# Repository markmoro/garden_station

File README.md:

Garden Station
==============

Single board garden watering controller based on Arduino.

This is a single board AT-MEGA controller.   This has an interface for a display, some LED indicators, inputs for moisture sensors and outputs for servo controller valves.   

Code is now added and the board has now been replaced with an SMD version.  The original prototype board is in the old folder, however there are some wiring issues with the shift registers which require some jumper wire.   This can be seen on the blog page photo.

More details are available on [http://makicity.com/](http://makicity.com/)

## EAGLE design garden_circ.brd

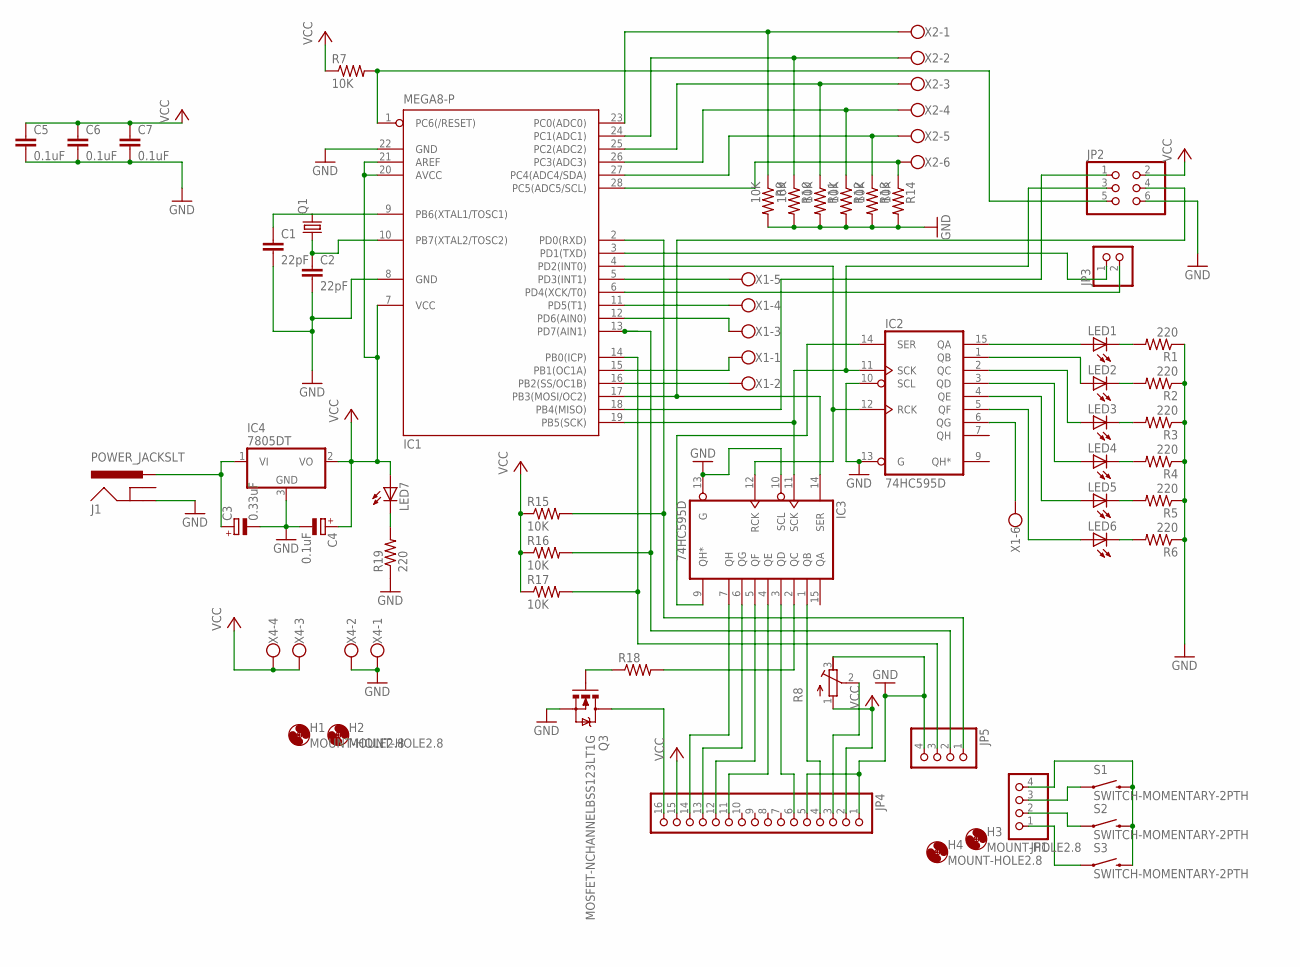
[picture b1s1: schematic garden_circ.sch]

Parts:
C1, C2: 22pF; 0805
C3: 0.33uF; SMC_C
C4: 0.1uF; SMC_C
C5, C6, C7: 0.1uF; 0805
H1, H2, H3, H4: MOUNT-HOLE2.8; 2,8
IC1: MEGA8-P; DIL28-3
IC2, IC3: 74HC595D; SO16
IC4: 7805DT; TO252
J1: POWER_JACKSLT; POWER_JACK_SLOT
JP1, JP5: PINHD-1X4; 1X04
JP2: PINHD-2X3; 2X03
JP3: PINHD-1X2; 1X02
JP4: PINHD-1X16; 1X16
LED1, LED2, LED3, LED4, LED5, LED6: LED3MM
LED7: LEDSML0805; SML0805
Q1: CRYSTALHC49UP; HC49UP
Q3: MOSFET-NCHANNELBSS123LT1G; SOT23
R1, R2, R3, R4, R5, R6, R19: 220; 0805
R7, R9, R10, R11, R12, R13, R14, R15, R16, R17: 10K; 0805
R8: R-TRIMM3202; RTRIM3202
R18: RESISTOR0805-RES; 0805
S1, S2, S3: SWITCH-MOMENTARY-2PTH; TACTILE-PTH
X1, X2: W237-136
X4: W237-4

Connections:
GND: C1.2, C2.2, C3.-, C4.-, C5.2, C6.2, C7.2, IC1.8 (GND), IC1.22 (GND), IC2.8 (GND), IC2.10 (SCL), IC2.13 (G), IC3.8 (GND), IC3.10 (SCL), IC3.13 (G), IC4.3 (GND), J1.GND@2 (GND), JP2.6, JP4.1, JP4.5, JP5.4, Q3.2 (S), R1.1, R2.1, R3.1, R4.1, R5.1, R6.1, R8.3 (A), R9.2, R10.2, R11.2, R12.2, R13.2, R14.2, R19.1, X4.1, X4.2
MISO: IC1.18 (PB4(MISO)), JP2.1
unnamed: C1.1, IC1.9 (PB6(XTAL1/TOSC1)), Q1.2
unnamed: C2.1, IC1.10 (PB7(XTAL2/TOSC2)), Q1.1
unnamed: LED1.K (C), R1.2
unnamed: LED2.K (C), R2.2
unnamed: LED3.K (C), R3.2
unnamed: LED4.K (C), R4.2
unnamed: LED5.K (C), R5.2
unnamed: LED6.K (C), R6.2
unnamed: IC2.6 (QG), X1.6
unnamed: IC1.1 (PC6(/RESET)), JP2.5, R7.2
unnamed: IC2.15 (QA), LED1.A
unnamed: IC2.1 (QB), LED2.A
unnamed: IC2.2 (QC), LED3.A
unnamed: IC2.3 (QD), LED4.A
unnamed: IC1.11 (PD5(T1)), X1.4
unnamed: IC2.4 (QE), LED5.A
unnamed: IC2.5 (QF), LED6.A
unnamed: IC1.6 (PD4(XCK/T0)), JP3.2
unnamed: IC1.19 (PB5(SCK)), IC2.11 (SCK), IC3.11 (SCK), JP2.3
unnamed: IC2.14 (SER), IC3.9 (QH*)
unnamed: IC1.12 (PD6(AIN0)), X1.3
unnamed: IC1.15 (PB1(OC1A)), X1.1
unnamed: IC1.24 (PC1(ADC1)), R10.1, X2.2
unnamed: IC3.3 (QD), JP4.6
unnamed: IC3.1 (QB), JP4.4
unnamed: IC3.7 (QH), JP4.14
unnamed: IC3.6 (QG), JP4.13
unnamed: IC3.5 (QF), JP4.12
unnamed: IC1.23 (PC0(ADC0)), R9.1, X2.1
unnamed: IC1.25 (PC2(ADC2)), R11.1, X2.3
unnamed: IC1.26 (PC3(ADC3)), R12.1, X2.4
unnamed: IC1.27 (PC4(ADC4/SDA)), R13.1, X2.5
unnamed: IC1.28 (PC5(ADC5/SCL)), R14.1, X2.6
unnamed: IC1.16 (PB2(SS/OC1B)), X1.2
unnamed: C3.+, IC4.1 (VI), J1.PWR
unnamed: IC1.2 (PD0(RXD)), JP5.1, R15.2
unnamed: IC1.13 (PD7(AIN1)), JP5.2, R16.2
unnamed: IC1.14 (PB0(ICP)), JP5.3, R17.2
unnamed: IC1.5 (PD3(INT1)), X1.5
unnamed: IC1.17 (PB3(MOSI/OC2)), IC3.14 (SER), JP2.4
unnamed: IC1.3 (PD1(TXD)), JP3.1
unnamed: IC1.4 (PD2(INT0)), IC2.12 (RCK), IC3.12 (RCK)
unnamed: JP4.3, R8.2 (S)
unnamed: IC3.4 (QE), JP4.11
unnamed: JP1.1, S3.1
unnamed: JP4.16, Q3.3 (D)
unnamed: Q3.1 (G), R18.1
unnamed: IC3.2 (QC), R18.2
unnamed: JP1.2, S2.1
unnamed: JP1.3, S1.1
unnamed: JP1.4, S1.3 (2), S2.3 (2), S3.3 (2)
unnamed: LED7.C, R19.2
VCC: C4.+, C5.1, C6.1, C7.1, IC1.7 (VCC), IC1.20 (AVCC), IC1.21 (AREF), IC2.16 (VCC), IC3.16 (VCC), IC4.2 (VO), JP2.2, JP4.2, JP4.15, LED7.A, R7.1, R8.1 (E), R15.1, R16.1, R17.1, X4.3, X4.4

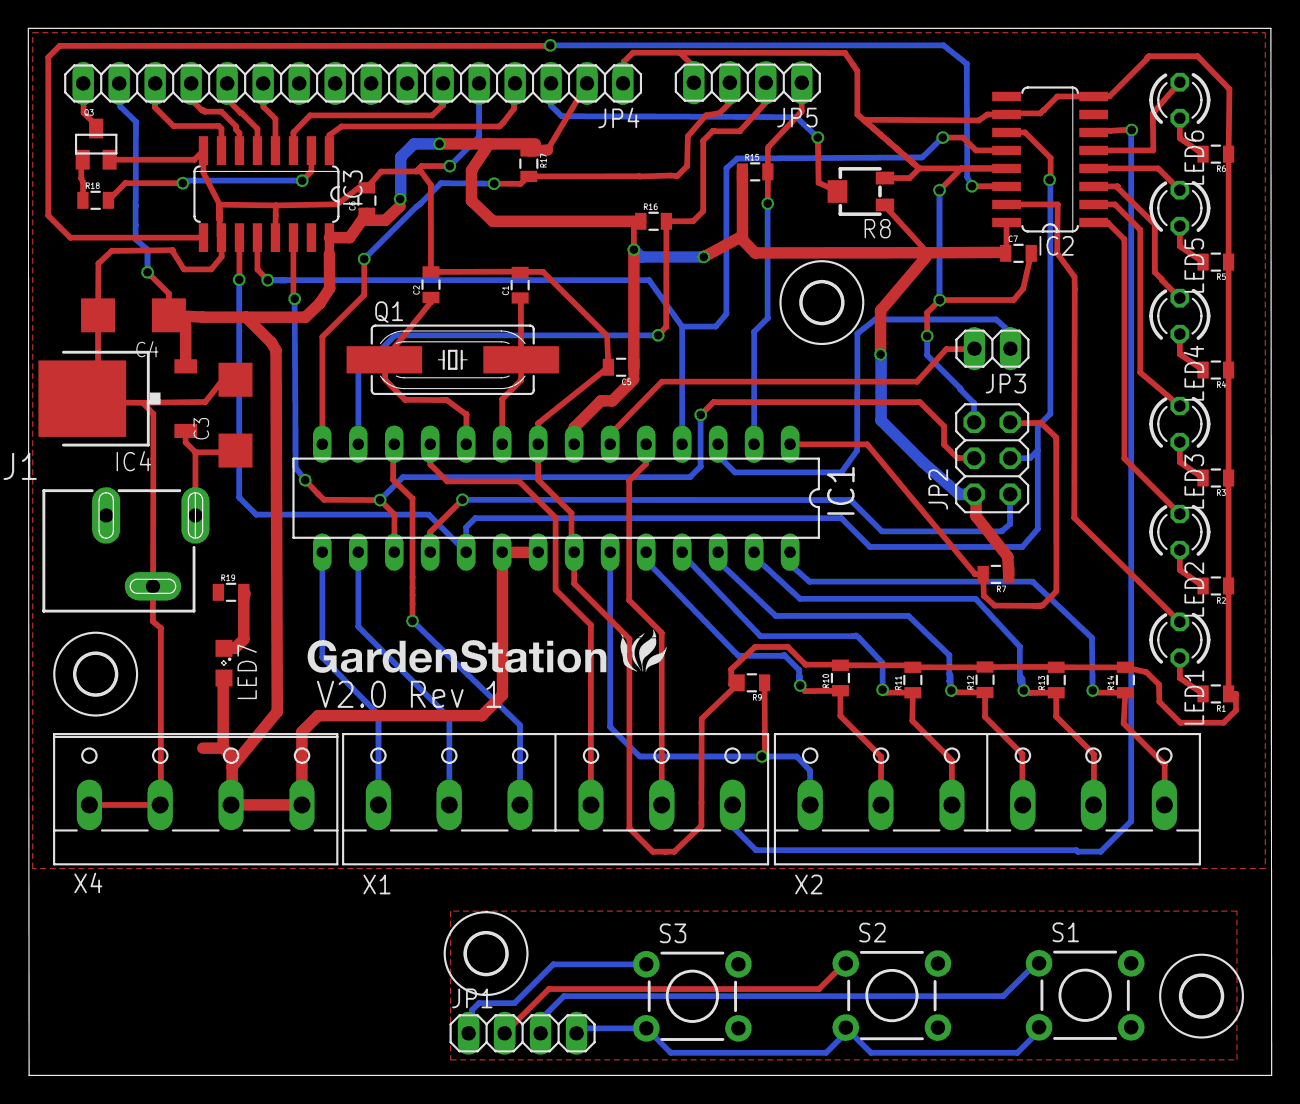
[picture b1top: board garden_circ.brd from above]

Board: 2 copper layers, 87.8 x 73.9 mm, 55 parts (0 on the bottom side), 55 nets.

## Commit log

2013-11-15 Initial Version
2013-12-08 Fixed shift register wiring
2014-02-09 Added code an SMD board
2014-02-09 Fixed README
2014-02-18 Added the code to powerdown backlight of LCD
2014-08-11 Added a few tweaks and power light

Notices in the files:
parts and their libraries:
SparkFun-Connectors: Licensing: CC v3.0 Share-Alike You are welcome to use this library for commercial purposes.
